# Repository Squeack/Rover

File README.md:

# Rover
6 wheel drive, 6 wheel steer rocker-bogie 'Mars rover'

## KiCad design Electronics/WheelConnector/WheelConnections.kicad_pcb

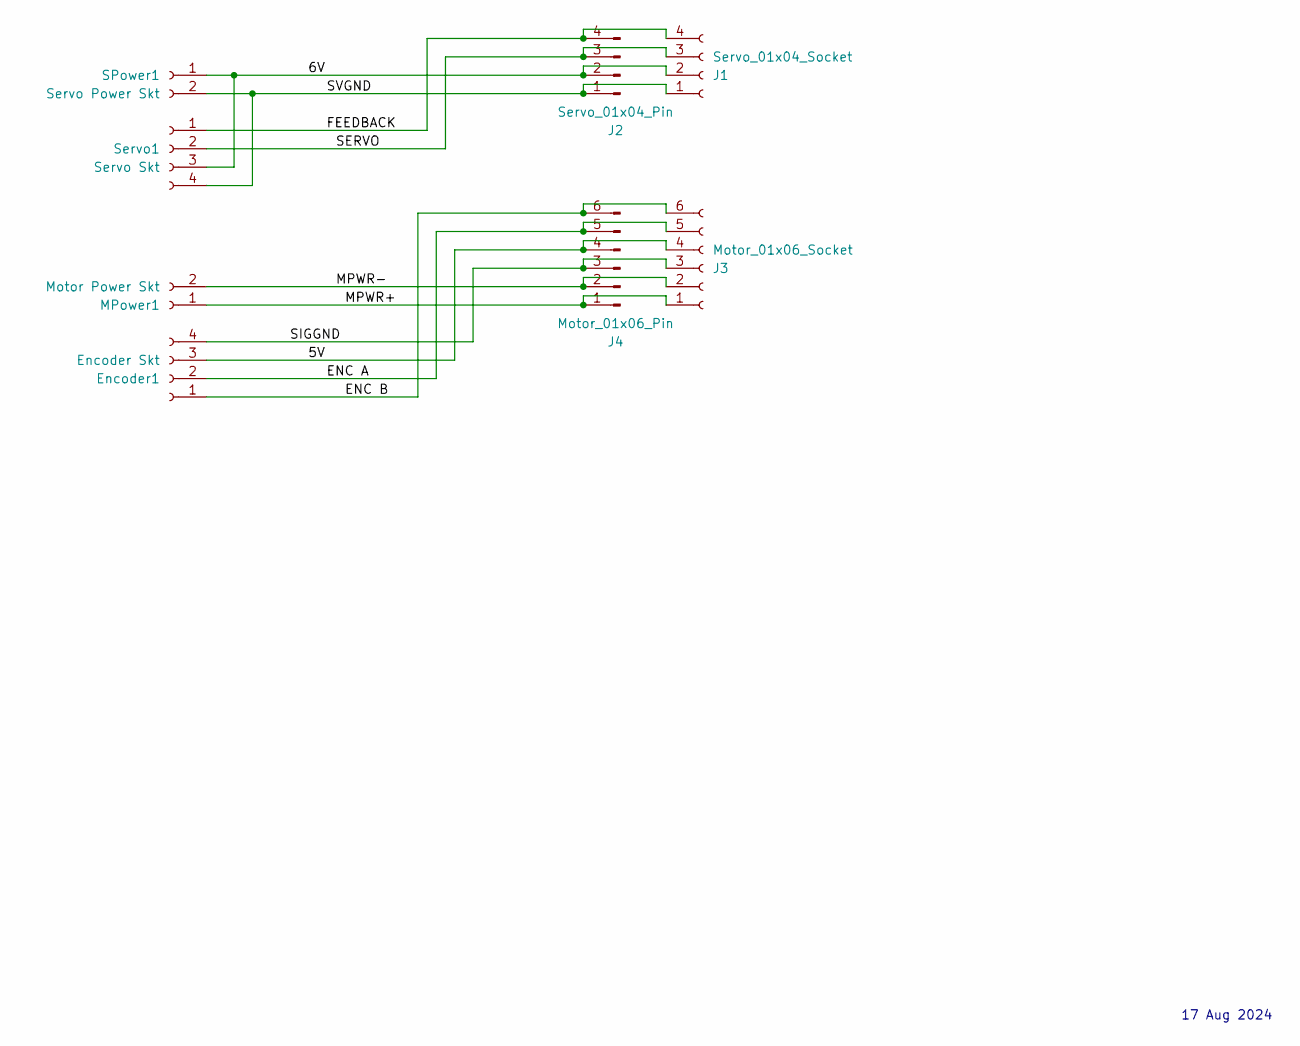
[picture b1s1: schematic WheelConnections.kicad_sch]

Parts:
Encoder1: Encoder Skt; JST_XH_B4B-XH-A_1x04_P2.50mm_Vertical
J1: Servo_01x04_Socket; JST_XH_B4B-XH-A_1x04_P2.50mm_Vertical
J2: Servo_01x04_Pin; PinHeader_1x04_P2.54mm_Vertical
J3: Motor_01x06_Socket; JST_XH_B6B-XH-A_1x06_P2.50mm_Vertical
J4: Motor_01x06_Pin; PinHeader_1x06_P2.54mm_Vertical
MPower1: Motor Power Skt; TerminalBlock_MetzConnect_Type101_RT01602HBWC_1x02_P5.08mm_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
SPower1: Servo Power Skt; TerminalBlock_MetzConnect_Type101_RT01602HBWC_1x02_P5.08mm_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
Servo1: Servo Skt; JST_XH_B4B-XH-A_1x04_P2.50mm_Vertical

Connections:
/5V: Encoder1.3, J3.4, J4.4
/6V: J1.2, J2.2, SPower1.1, Servo1.3
/ENC A: Encoder1.2, J3.5, J4.5
/ENC B: Encoder1.1, J3.6, J4.6
/FEEDBACK: J1.4, J2.4, Servo1.1
/MPWR+: J3.1, J4.1, MPower1.1
/MPWR-: J3.2, J4.2, MPower1.2
/SERVO: J1.3, J2.3, Servo1.2
/SIGGND: Encoder1.4, J3.3, J4.3
/SVGND: J1.1, J2.1, SPower1.2, Servo1.4

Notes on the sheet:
17 Aug 2024

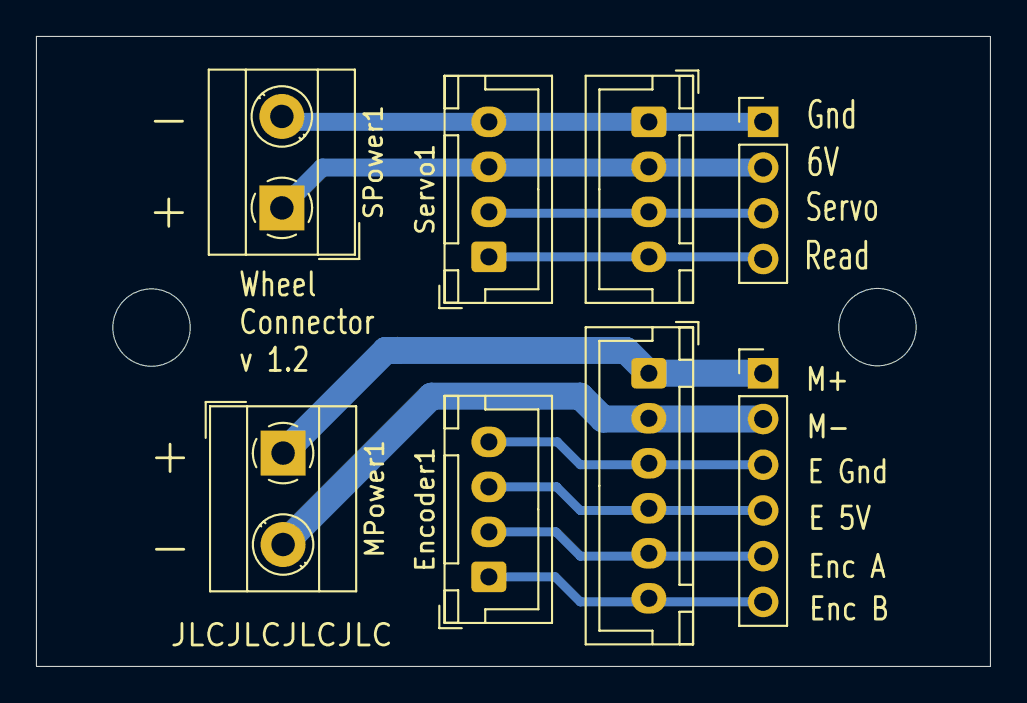
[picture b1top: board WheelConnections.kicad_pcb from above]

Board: 2 copper layers, 53.0 x 35.0 mm, 8 parts (0 on the bottom side), 10 nets.

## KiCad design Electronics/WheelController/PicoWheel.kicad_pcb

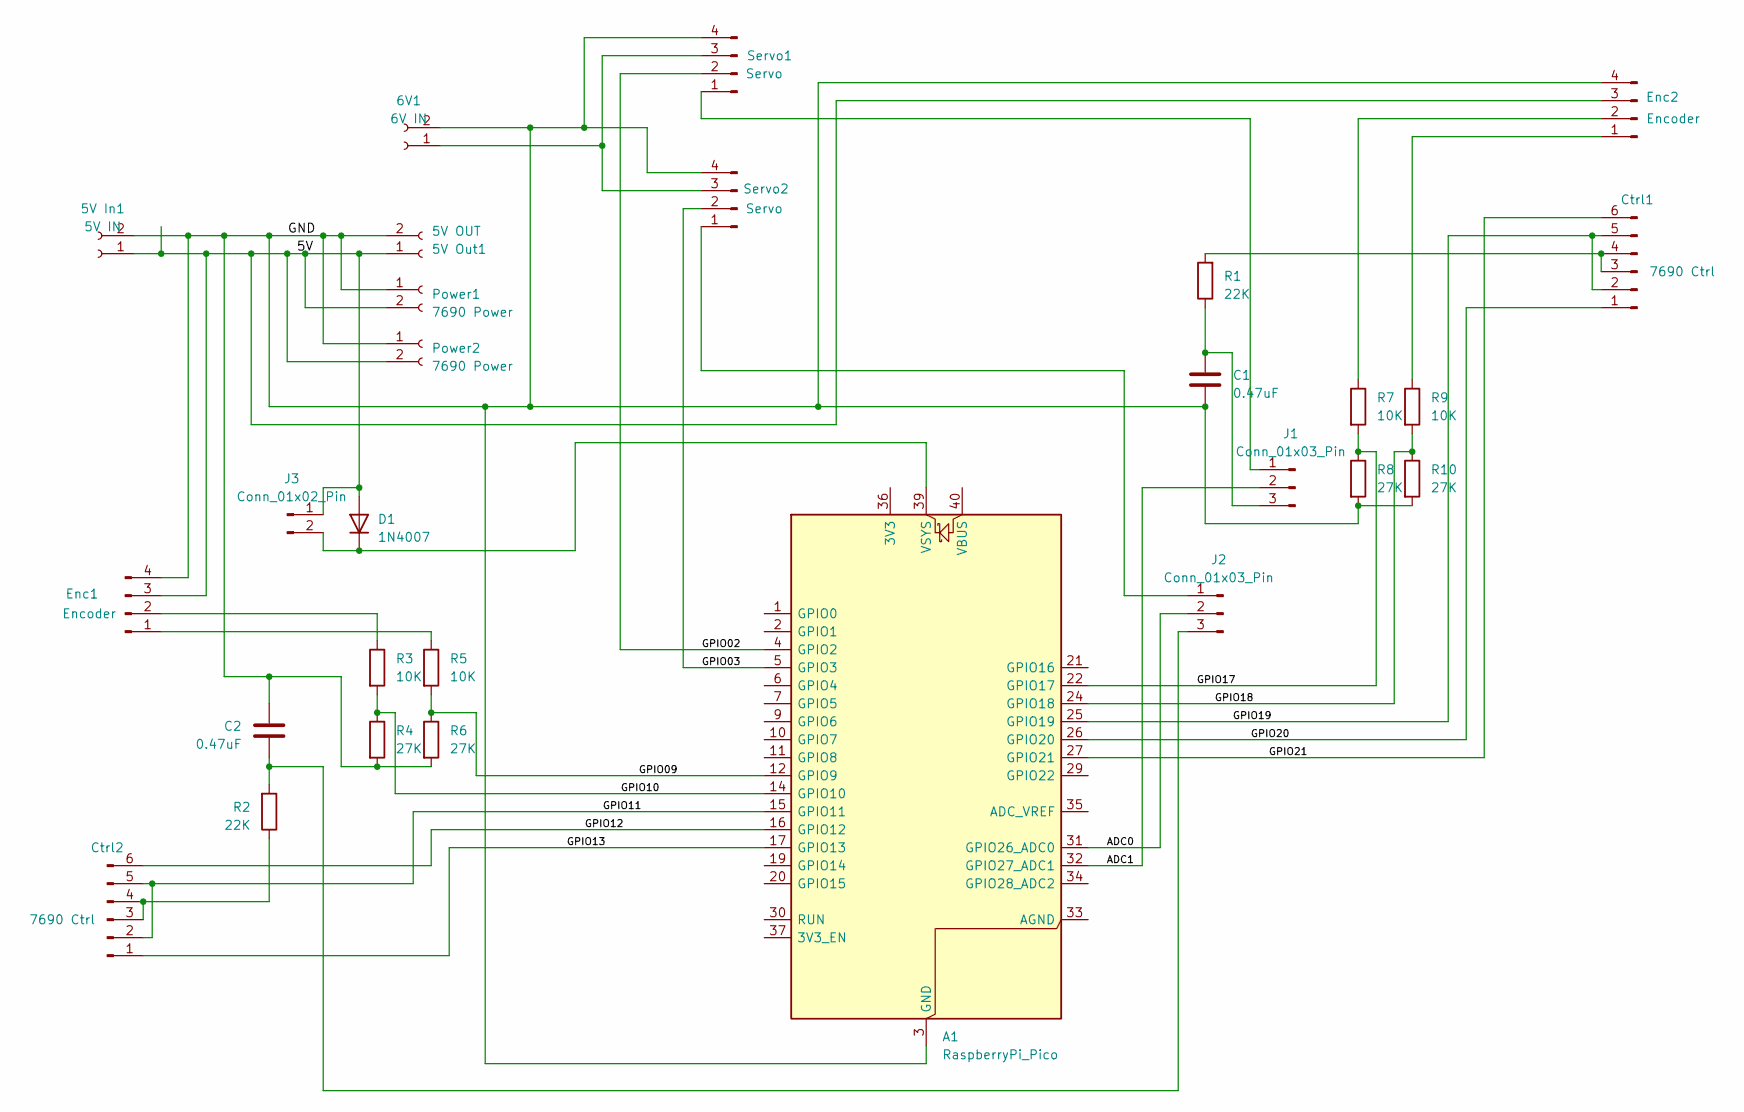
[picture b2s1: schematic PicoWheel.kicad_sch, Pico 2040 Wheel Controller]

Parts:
5V In1: 5V IN; JST_XH_B2B-XH-A_1x02_P2.50mm_Vertical
5V Out1: 5V OUT; JST_XH_B2B-XH-A_1x02_P2.50mm_Vertical
6V1: 6V IN; JST_XH_B2B-XH-A_1x02_P2.50mm_Vertical
A1: RaspberryPi_Pico; RaspberryPi_Pico_Common
C1, C2: 0.47uF; CP_Radial_D6.3mm_P2.50mm
Ctrl1, Ctrl2: 7690 Ctrl; JST_XH_B6B-XH-A_1x06_P2.50mm_Vertical
D1: 1N4007; D_DO-41_SOD81_P10.16mm_Horizontal
Enc1, Enc2: Encoder; JST_XH_B4B-XH-A_1x04_P2.50mm_Vertical
J1, J2: Conn_01x03_Pin; PinHeader_1x03_P2.54mm_Vertical
J3: Conn_01x02_Pin; PinHeader_1x02_P2.54mm_Vertical
Power1, Power2: 7690 Power; JST_XH_B2B-XH-A_1x02_P2.50mm_Vertical
R1, R2: 22K; R_Axial_DIN0207_L6.3mm_D2.5mm_P7.62mm_Horizontal
R3, R5, R7, R9: 10K; R_Axial_DIN0204_L3.6mm_D1.6mm_P2.54mm_Vertical
R4, R6, R8, R10: 27K; R_Axial_DIN0204_L3.6mm_D1.6mm_P2.54mm_Vertical
Servo1, Servo2: Servo; JST_XH_B4B-XH-A_1x04_P2.50mm_Vertical

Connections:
/5V: 5V In1.1, 5V Out1.1, D1.2 (A), Enc1.3, Enc2.3, J3.1, Power1.2, Power2.2
/ADC0: A1.31 (GPIO26_ADC0), J2.2
/ADC1: A1.32 (GPIO27_ADC1), J1.2
/GND: 5V In1.2, 5V Out1.2, 6V1.2, A1.3 (GND), A1.8 (GND), A1.13 (GND), A1.18 (GND), A1.23 (GND), A1.28 (GND), A1.38 (GND), C1.2, C2.2, Enc1.4, Enc2.4, Power1.1, Power2.1, R4.2, R6.2, R8.2, R10.2, Servo1.4, Servo2.4
/GPIO02: A1.4 (GPIO2), Servo1.2
/GPIO03: A1.5 (GPIO3), Servo2.2
/GPIO09: A1.12 (GPIO9), R5.2, R6.1
/GPIO10: A1.14 (GPIO10), R3.2, R4.1
/GPIO11: A1.15 (GPIO11), Ctrl2.2, Ctrl2.5
/GPIO12: A1.16 (GPIO12), Ctrl2.6
/GPIO13: A1.17 (GPIO13), Ctrl2.1
/GPIO17: A1.22 (GPIO17), R7.2, R8.1
/GPIO18: A1.24 (GPIO18), R9.2, R10.1
/GPIO19: A1.25 (GPIO19), Ctrl1.2, Ctrl1.5
/GPIO20: A1.26 (GPIO20), Ctrl1.1
/GPIO21: A1.27 (GPIO21), Ctrl1.6
unnamed: 6V1.1, Servo1.3, Servo2.3
unnamed: A1.39 (VSYS), D1.1 (K), J3.2
unnamed: Ctrl1.3, Ctrl1.4, R1.2
unnamed: Ctrl2.3, Ctrl2.4, R2.1
unnamed: Enc1.1, R5.1
unnamed: Enc1.2, R3.1
unnamed: Enc2.1, R9.1
unnamed: Enc2.2, R7.1
unnamed: J1.1, Servo1.1
unnamed: C1.1, J1.3, R1.1
unnamed: J2.1, Servo2.1
unnamed: C2.1, J2.3, R2.2

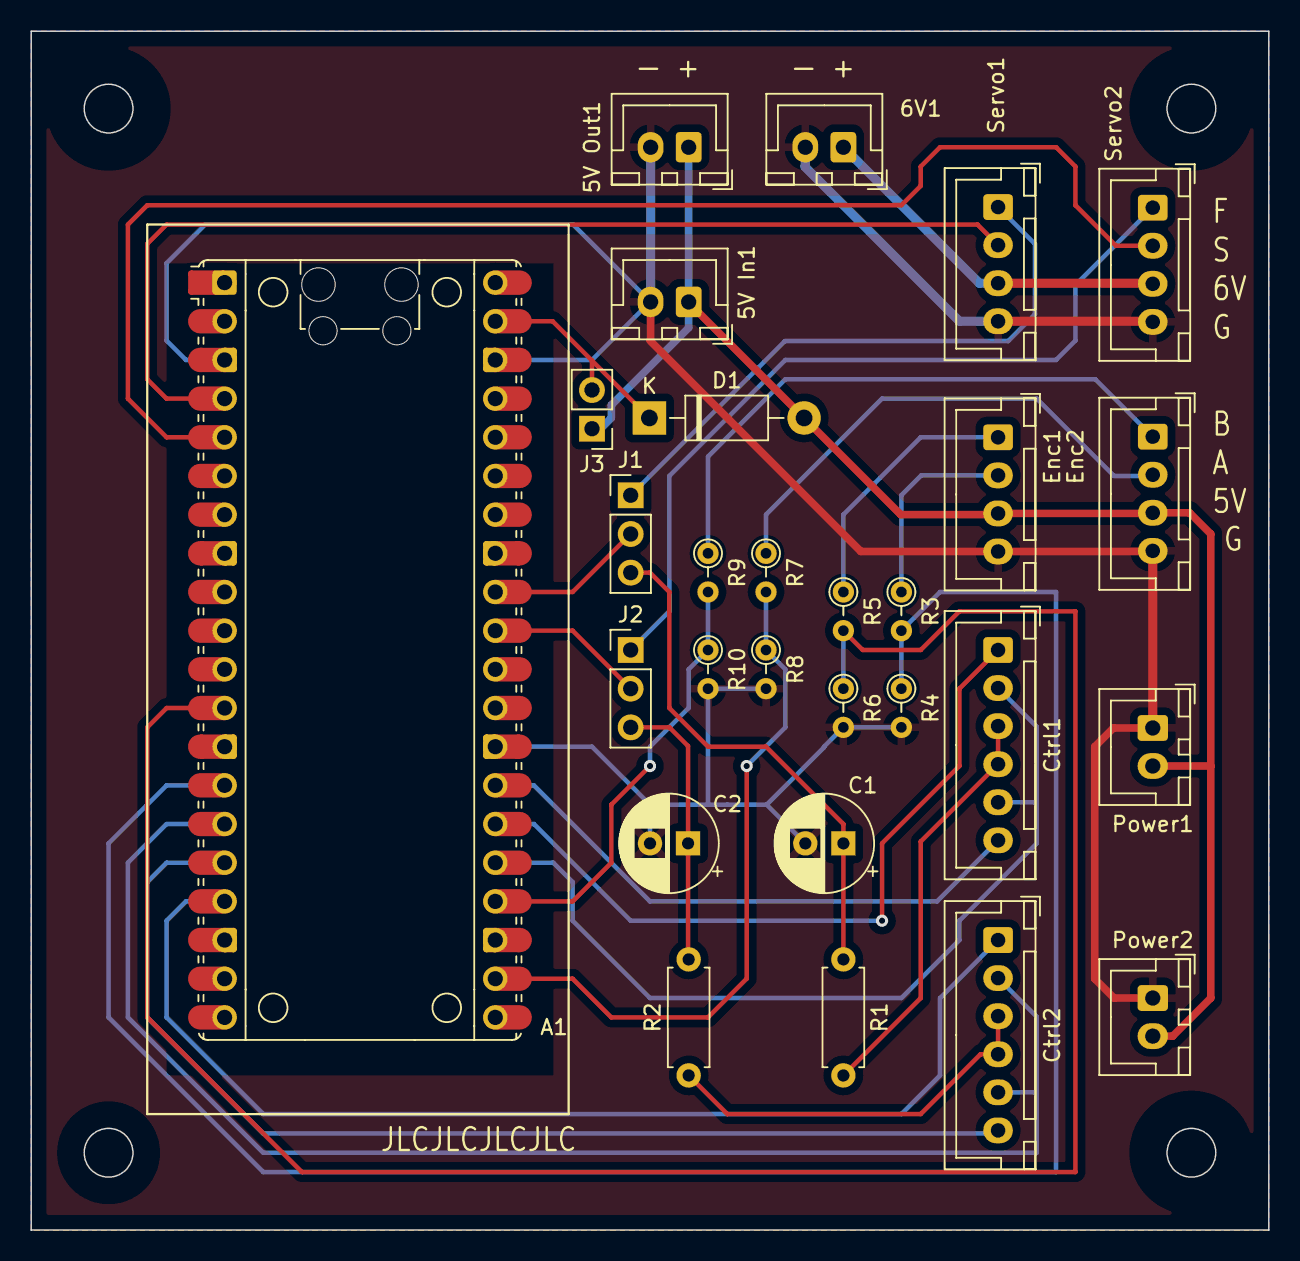
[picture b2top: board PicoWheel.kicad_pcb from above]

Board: 2 copper layers, 81.3 x 78.7 mm, 28 parts (0 on the bottom side), 28 nets.

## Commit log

2026-04-24 Add files via upload
    Licence/License file
2026-04-25 Fixed image link
